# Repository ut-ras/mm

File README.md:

# Micromouse 2019
UT RAS Micromouse repository for 2019

The repository is structured with hardware eagle files under the [pcb](./pcb) directory and the esp-idf projects under the [software/test-programs](./software/test-programs) directory. To make or flash a program move into a project folder corresponding to that program and run either `make` or `make flash` respectively.
## Setup Software
- Download and Install esp-idf which can be found [here](https://docs.espressif.com/projects/esp-idf/en/latest/get-started/#setting-up-development-environment)
- Download and build software
```bash
git clone https://github.com/ut-ras/mm19
cd software
make
```

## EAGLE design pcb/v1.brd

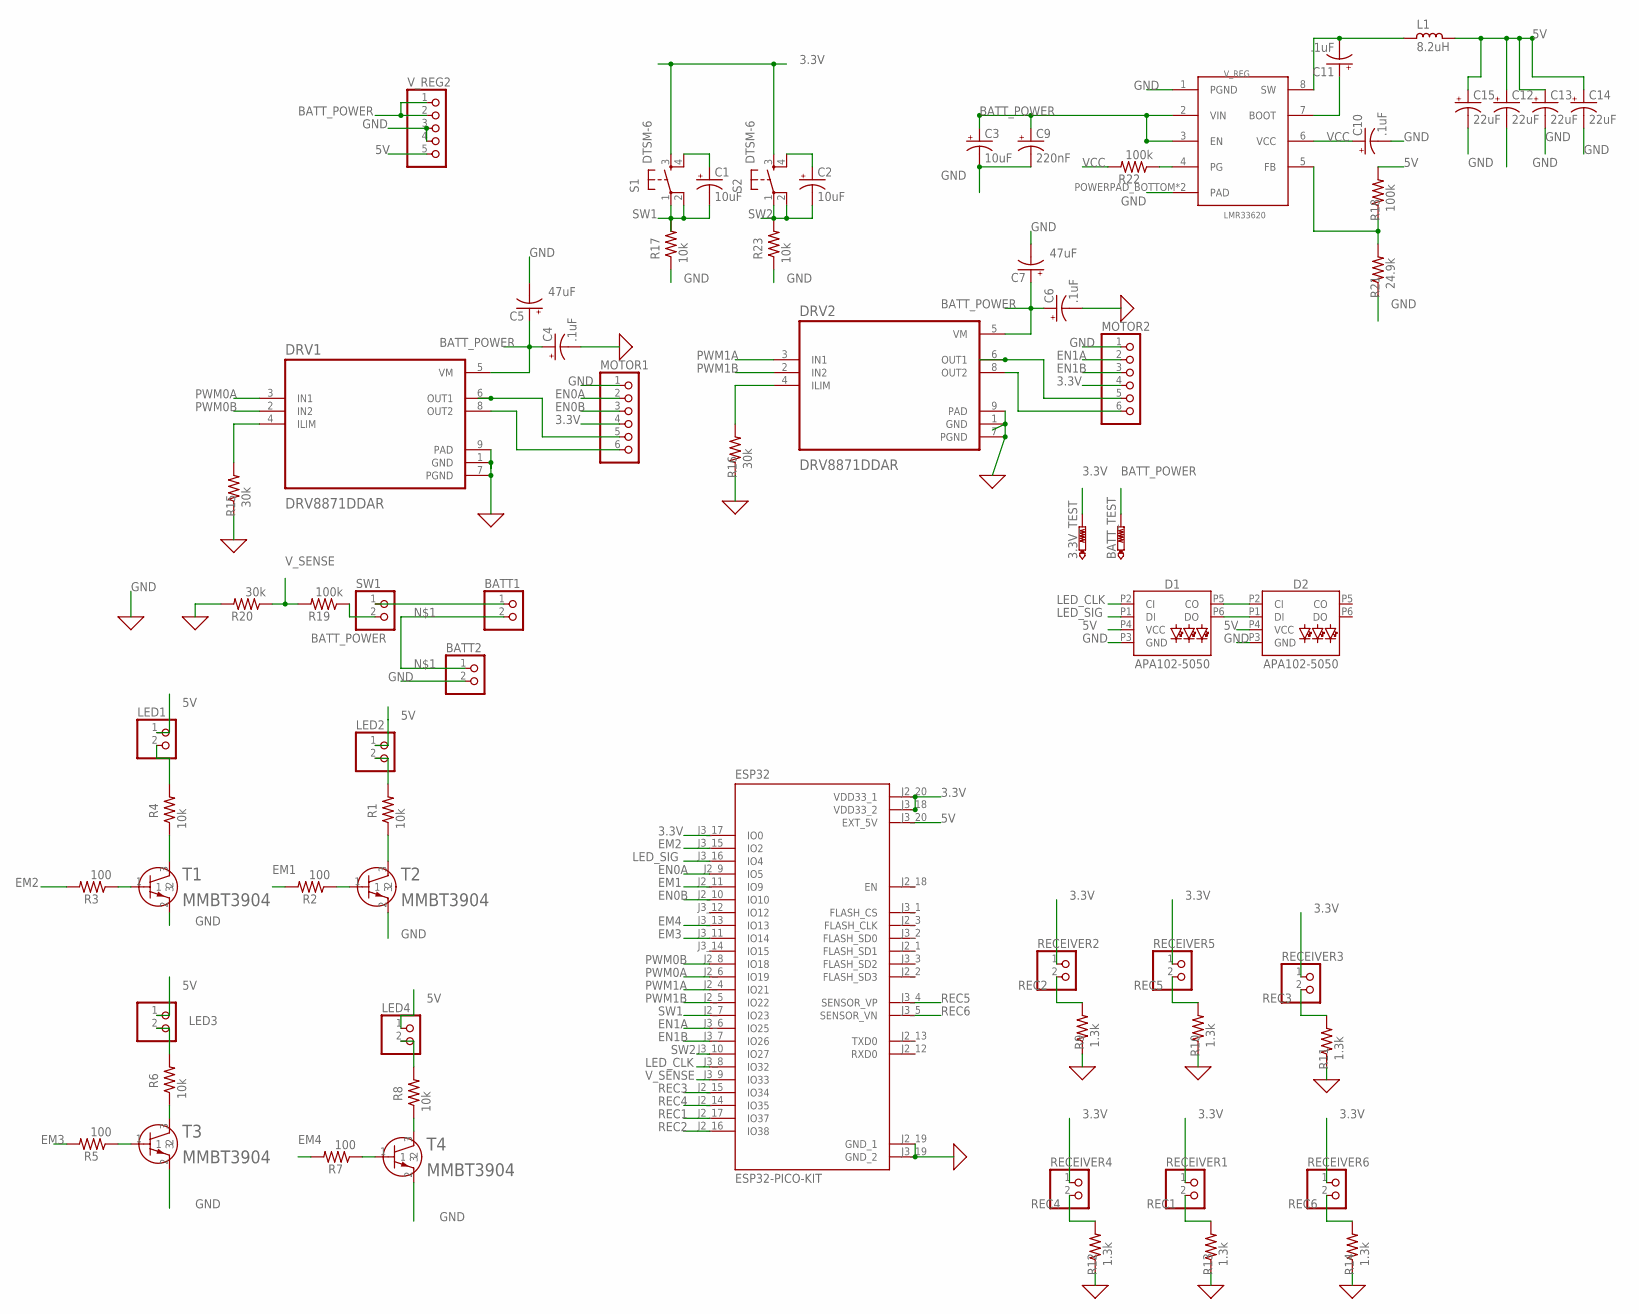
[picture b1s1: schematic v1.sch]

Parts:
3.3V_TEST: PTR1B1,27; B1,27
BATT1, BATT2: PINHD-1X2; 1X02
BATT_TEST: PTR1B1,27; B1,27
C1, C2, C3: 10uF; A/3216-18R
C4, C6, C10, C11: .1uF; A/3216-18R
C5, C7: 47uF; 150CLZ-0810
C9: 220nF; A/3216-18R
C12, C13, C14, C15: 22uF; A/3216-18R
D1, D2: APA102-5050
DRV1, DRV2: DRV8871DDAR; SOIC127P600X170-8N
ESP32: ESP32-PICO-KIT; XCVR_ESP32-PICO-KIT
L1: 8.2uH; PM1812
LED1, LED2, LED3, LED4: PINHD-1X2; 1X02
MOTOR1, MOTOR2: PINHD-1X6; 1X06
R1, R4, R6, R8, R17, R23: 10k; M1206
R2, R3, R5, R7: 100; M1206
R9, R10, R11, R12, R13, R14: 1.3k; M1206
R15, R16, R20: 30k; M1206
R18, R19, R22: 100k; M1206
R21: 24.9k; M1206
RECEIVER1, RECEIVER2, RECEIVER3, RECEIVER4, RECEIVER5, RECEIVER6: PINHD-1X2; 1X02
S1, S2: DTSM-6
SW1: PINHD-1X2; 1X02
T1, T2, T3, T4: MMBT3904; SOT23
V_REG: LMR33620; SO-8_POWERPAD
V_REG2: PINHD-1X5; 1X05

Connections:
3.3V: 3.3V_TEST.TP, ESP32.J2_20 (VDD33_1), ESP32.J3_17 (IO0), ESP32.J3_18 (VDD33_2), MOTOR1.4, MOTOR2.4, RECEIVER1.1, RECEIVER2.1, RECEIVER3.1, RECEIVER4.1, RECEIVER5.1, RECEIVER6.1, S1.3, S2.3
5V: C12.+, C13.+, C14.+, C15.+, D1.P4 (VCC), D2.P4 (VCC), ESP32.J3_20 (EXT_5V), L1.1, LED1.1, LED2.1, LED3.1, LED4.1, R18.2, V_REG2.5
BATT_POWER: BATT_TEST.TP, C3.+, C4.+, C5.+, C6.+, C7.+, C9.+, DRV1.5 (VM), DRV2.5 (VM), R19.1, SW1.2, V_REG.2 (VIN), V_REG.3 (EN), V_REG2.1, V_REG2.2
EM1: ESP32.J2_11 (IO9), R2.2
EM2: ESP32.J3_15 (IO2), R3.2
EM3: ESP32.J3_11 (IO14), R5.2
EM4: ESP32.J3_13 (IO13), R7.2
EN0A: ESP32.J2_9 (IO5), MOTOR1.2
EN0B: ESP32.J2_10 (IO10), MOTOR1.3
EN1A: ESP32.J3_6 (IO25), MOTOR2.2
EN1B: ESP32.J3_7 (IO26), MOTOR2.3
GND: BATT2.2, C3.-, C4.-, C5.-, C6.-, C7.-, C9.-, C10.-, C12.-, C13.-, C14.-, C15.-, D1.P3 (GND), D2.P3 (GND), DRV1.1 (GND), DRV1.7 (PGND), DRV1.9 (PAD), DRV2.1 (GND), DRV2.7 (PGND), DRV2.9 (PAD), ESP32.J2_19 (GND_1), ESP32.J3_19 (GND_2), MOTOR1.1, MOTOR2.1, R9.1, R10.1, R11.1, R12.1, R13.1, R14.1, R15.1, R16.1, R17.1, R20.2, R21.1, R23.1, T1.2, T2.2, T3.2, T4.2, V_REG.1 (PGND), V_REG.POWERPAD_BOTTOM (PAD), V_REG.POWERPAD_TOP (PAD), V_REG2.3, V_REG2.4
LED3: LED3.2, R6.2
LED_CLK: D1.P2 (CI), ESP32.J3_8 (IO32)
LED_SIG: D1.P1 (DI), ESP32.J3_16 (IO4)
unnamed: BATT1.2, BATT2.1
unnamed: BATT1.1, SW1.1
unnamed: C1.+, S1.4
unnamed: R2.1, T2.1
unnamed: LED2.2, R1.2
unnamed: R1.1, T2.3
unnamed: LED1.2, R4.2
unnamed: R4.1, T1.3
unnamed: R5.1, T3.1
unnamed: R6.1, T3.3
unnamed: R7.1, T4.1
unnamed: LED4.2, R8.2
unnamed: R8.1, T4.3
unnamed: DRV1.8 (OUT2), MOTOR1.6
unnamed: DRV1.6 (OUT1), MOTOR1.5
unnamed: DRV2.8 (OUT2), MOTOR2.6
unnamed: DRV2.6 (OUT1), MOTOR2.5
unnamed: DRV2.4 (ILIM), R16.2
unnamed: C2.+, S2.4
unnamed: R18.1, R21.2, V_REG.5 (FB)
unnamed: DRV1.4 (ILIM), R15.2
unnamed: C11.+, V_REG.7 (BOOT)
unnamed: C11.-, L1.2, V_REG.8 (SW)
unnamed: D1.P5 (CO), D2.P2 (CI)
unnamed: D1.P6 (DO), D2.P1 (DI)
PG: R22.1, V_REG.4 (PG)
PWM0A: DRV1.3 (IN1), ESP32.J2_6 (IO19)
PWM0B: DRV1.2 (IN2), ESP32.J2_8 (IO18)
PWM1A: DRV2.3 (IN1), ESP32.J2_4 (IO21)
PWM1B: DRV2.2 (IN2), ESP32.J2_5 (IO22)
REC1: ESP32.J2_17 (IO37), R13.2, RECEIVER1.2
REC2: ESP32.J2_16 (IO38), R9.2, RECEIVER2.2
REC3: ESP32.J2_15 (IO34), R11.2, RECEIVER3.2
REC4: ESP32.J2_14 (IO35), R12.2, RECEIVER4.2
REC5: ESP32.J3_4 (SENSOR_VP), R10.2, RECEIVER5.2
REC6: ESP32.J3_5 (SENSOR_VN), R14.2, RECEIVER6.2
SW1: C1.-, ESP32.J2_7 (IO23), R17.2, S1.1, S1.2
SW2: C2.-, ESP32.J3_10 (IO27), R23.2, S2.1, S2.2
T1: R3.1, T1.1
VCC: C10.+, R22.2, V_REG.6 (VCC)
V_SENSE: ESP32.J3_9 (IO33), R19.2, R20.1

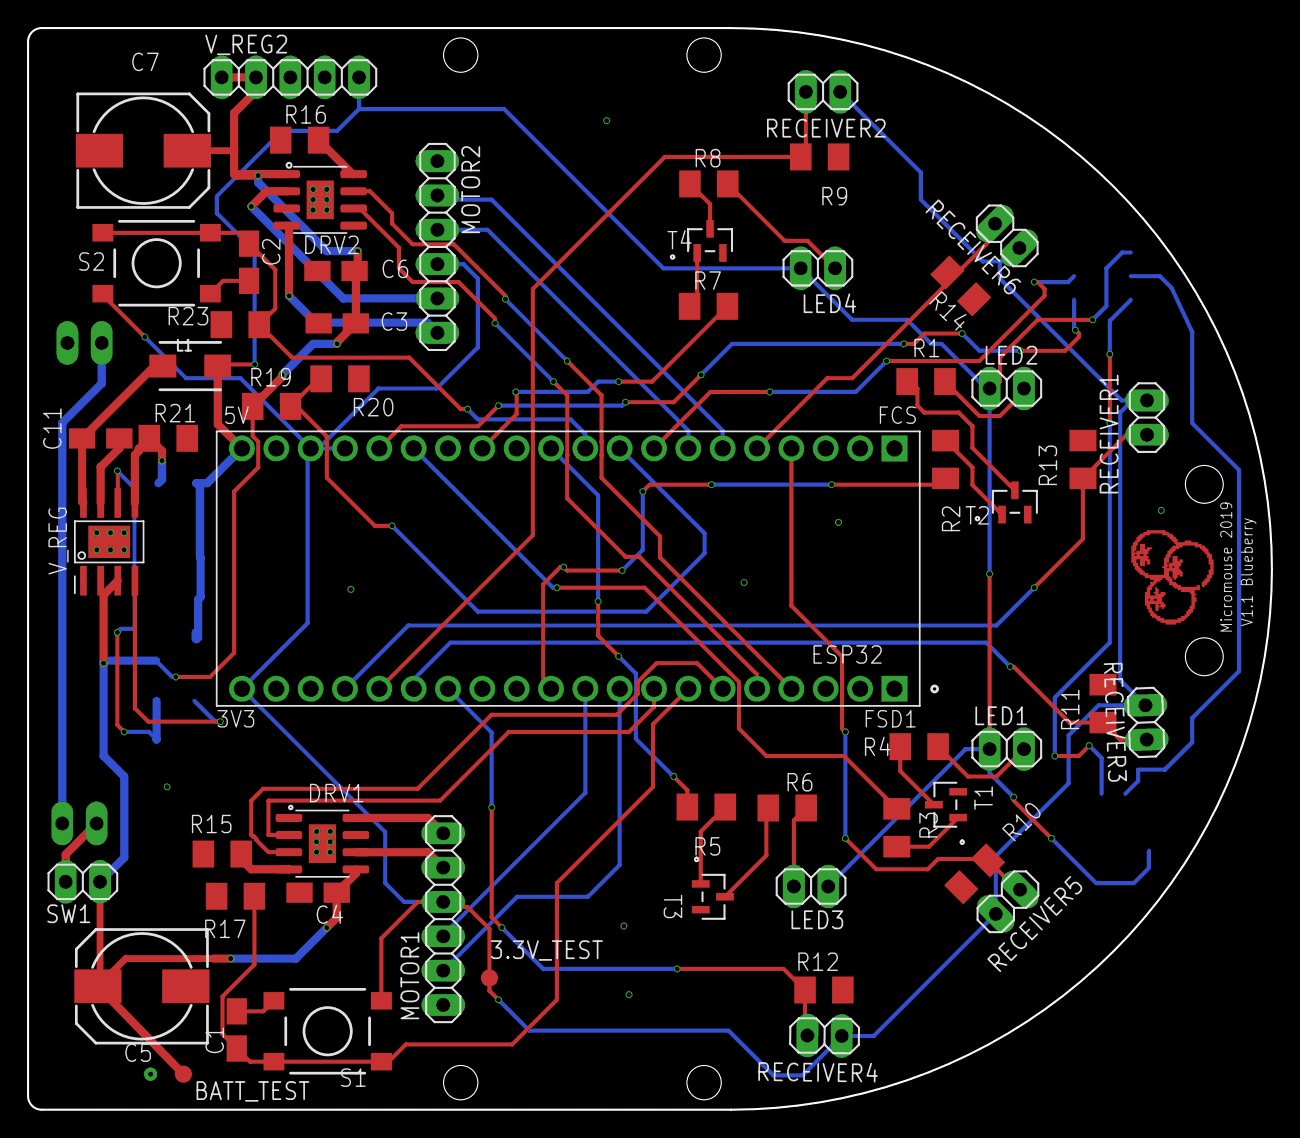
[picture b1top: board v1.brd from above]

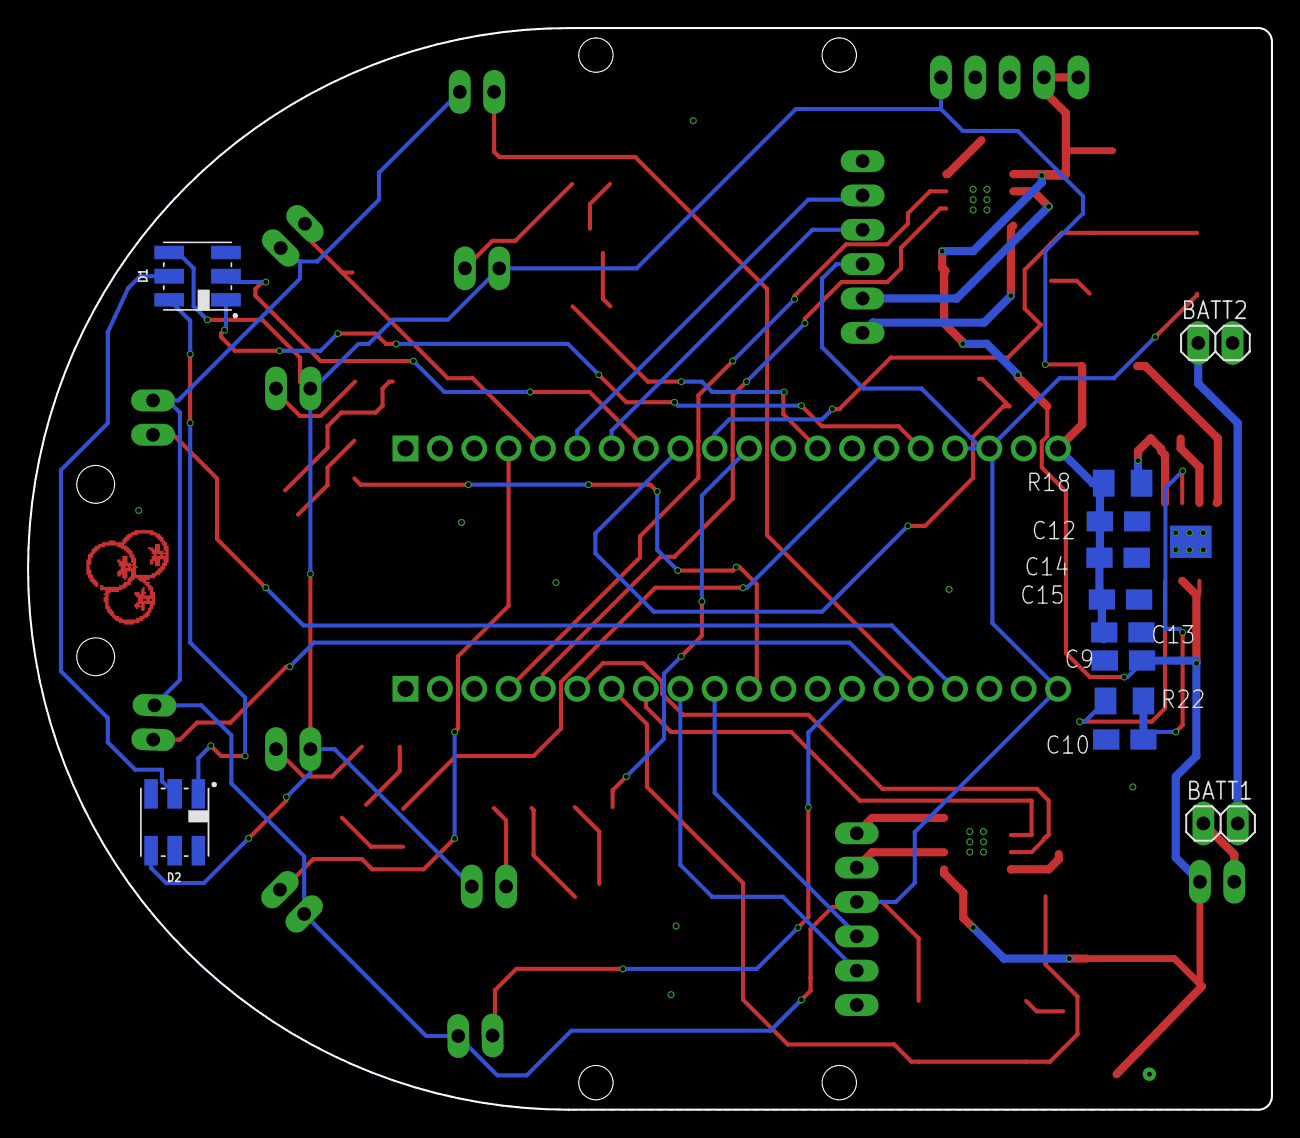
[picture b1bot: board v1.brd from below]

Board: 2 copper layers, 92.0 x 80.0 mm, 68 parts (12 on the bottom side), 56 nets.

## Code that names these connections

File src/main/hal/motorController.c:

#include "driver/mcpwm.h"

#define GPIO_PWM0A_OUT 19  // Set GPIO 19 as PWM0A
#define GPIO_PWM0B_OUT 18  // Set GPIO 18 as PWM0B
#define GPIO_PWM1A_OUT 22  // Set GPIO 22 as PWM1A
#define GPIO_PWM1B_OUT 21  // Set GPIO 21 as PWM1B

/**
 * @brief Configure whole MCPWM module
 */
static void mcpwm_frequency_initialize() {
  mcpwm_config_t pwm_config;
  pwm_config.frequency = 100;  // frequency = 100Hz
  pwm_config.cmpr_a = 0.0;     // duty cycle of PWMxA = 0.0%
  pwm_config.cmpr_b = 0.0;     // duty cycle of PWMxb = 0.0%
  pwm_config.counter_mode = MCPWM_UP_COUNTER;
  pwm_config.duty_mode = MCPWM_DUTY_MODE_0;
  mcpwm_init(
      MCPWM_UNIT_0, MCPWM_TIMER_0,
      &pwm_config);  // Configure PWM0A(19) & PWM0B(18) with above settings
  // connect 19 and 18 to a single motors
  pwm_config.frequency = 100;  // frequency = 100Hz
  pwm_config.cmpr_a = 0.0;     // duty cycle of PWMxA = 0.0%
  pwm_config.cmpr_b = 0.0;     // duty cycle of PWMxb = 0.0%
  pwm_config.counter_mode = MCPWM_UP_COUNTER;
  pwm_config.duty_mode = MCPWM_DUTY_MODE_0;
  mcpwm_init(
      MCPWM_UNIT_0, MCPWM_TIMER_1,
      &pwm_config);  // Configure PWM1A(21) & PWM1B(22) with above settings
}

/*
 * Call this initialize before starting to set speed of the both motors
 */
void mcpwm_initialize() {
  printf("initializing mcpwm gpio...\n");
  mcpwm_gpio_init(MCPWM_UNIT_0, MCPWM0A, GPIO_PWM0A_OUT);
  mcpwm_gpio_init(MCPWM_UNIT_0, MCPWM0B, GPIO_PWM0B_OUT);
  mcpwm_gpio_init(MCPWM_UNIT_0, MCPWM1A, GPIO_PWM1A_OUT);
  mcpwm_gpio_init(MCPWM_UNIT_0, MCPWM1B, GPIO_PWM1B_OUT);
  mcpwm_frequency_initialize();
}

// speed is positive to go forward, negative to go backward. -100 to 100.
void setLeftSpeed(double speed) {
  if (speed > 0) {
    mcpwm_set_signal_low(MCPWM_UNIT_0, MCPWM_TIMER_1, MCPWM_OPR_B);
    mcpwm_set_duty(MCPWM_UNIT_0, MCPWM_TIMER_1, MCPWM_OPR_A, speed);
    mcpwm_set_duty_type(MCPWM_UNIT_0, MCPWM_TIMER_1, MCPWM_OPR_A,
                        MCPWM_DUTY_MODE_0);
  } else {
    mcpwm_set_signal_low(MCPWM_UNIT_0, MCPWM_TIMER_1, MCPWM_OPR_A);
    mcpwm_set_duty(MCPWM_UNIT_0, MCPWM_TIMER_1, MCPWM_OPR_B, -speed);
    mcpwm_set_duty_type(MCPWM_UNIT_0, MCPWM_TIMER_1, MCPWM_OPR_B,
                        MCPWM_DUTY_MODE_0);
  }
}

// speed is positive to go forward, negative to go backward. -100 to 100.
void setRightSpeed(double speed) {
  if (speed > 0) {
    mcpwm_set_signal_low(MCPWM_UNIT_0, MCPWM_TIMER_0, MCPWM_OPR_B);
    mcpwm_set_duty(MCPWM_UNIT_0, MCPWM_TIMER_0, MCPWM_OPR_A, speed);
    mcpwm_set_duty_type(MCPWM_UNIT_0, MCPWM_TIMER_0, MCPWM_OPR_A,
                        MCPWM_DUTY_MODE_0);
  } else {
    mcpwm_set_signal_low(MCPWM_UNIT_0, MCPWM_TIMER_0, MCPWM_OPR_A);
    mcpwm_set_duty(MCPWM_UNIT_0, MCPWM_TIMER_0, MCPWM_OPR_B, -speed);
    mcpwm_set_duty_type(MCPWM_UNIT_0, MCPWM_TIMER_0, MCPWM_OPR_B,
                        MCPWM_DUTY_MODE_0);
  }
}

void setMotors(float left, float right) {
  setLeftSpeed(left);
  setRightSpeed(-right);
}

void stopMotors(void) { setMotors(0.0, 0.0); }

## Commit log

2018-10-19 added high level algorithm and function implementations for simulator testing
2018-10-24 first commit. V1.0 implementation of classes for the simulation and C/C++ conversion. Documented. Needs driver with algorithm rebuilt. Needs basic testing driver.
2018-10-26 main algorithm v2 complete (probably), needs testing in simulator
2018-10-31 Added ADC testing files for esp
2018-11-08 updated working class and algorithm files for mm, now to translate into C and continue testing
2018-11-30 commited start of C port
2018-11-30 Neighbor.h, .c compiles
2018-11-30 unit tested, works
2018-12-01 updating Mouse.c...
2018-12-01 removed bool for Neighbor, replaced with a -1, 0, 1 and a #define UNKNOWN, TRUE, FALSE in the main mouse method that uses neighbor's pathbool; cleaned up control flow for findDir in mouse.c
2018-12-01 finished implementing what I can for Mouse.h, needs low level movement functions and abstracted testing moving functions as well as unit testing. Also needs Node.c to be implemented.
2018-12-08 wrote up node.c, alterations to neighbor, built a main tester and a makefile, currently unit testing looks good, needs to finish implmenting and rebuilding addRelation method of node.c, also testing 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
2018-12-08 rebuilt main to test cohesive classes, edited makefile, works, needs sensor functions to test actual mazesolving, also addrelations needs to be completed
2018-12-31 Added ESP initial files
2019-01-03 setup basic working client for c port of mmsim, processes wall commands and movement
2019-01-26 removed testing code that used weird ESP stuff
2019-02-20 commit from local before disk wipe
2019-02-20 untested hal code
2019-03-09 starting structure implementation of cpp port
2019-03-30 working encoders
2019-03-30 initialize second encoder
2019-03-30 detect stop as a direction
2019-03-30 Fixed merge conflig
2019-04-03 Cleaned up and organized hal #2
2019-04-04 additional refactoring
2019-04-08 Changed 5V receiver inputs to 3.3V
2019-04-08 Added Smd led
2019-04-08 Fixed led positioning and adc pins
2019-04-08 Changed 5V line
2019-04-08 Changed pin placement
2019-04-08 Flipped the back sensor resistors
2019-04-08 Evened out the holes to make pcb look nicer
2019-04-10 Changed the voltage regulator and updated the pcb
2019-04-10 Changed the resistive voltage divider values
2019-04-10 Added ground plane
2019-04-13 Added Strawberry
2019-04-13 initial pid code, pid_ctl unfinished
2019-04-13 Changed strawberry and caps. Added gerber files
2019-04-13 Last minute touches to PCB Moved headers for motor and led to not interfere with nuts. Made ground plane solid instead of hatched. Fixed silkscreen overlap. Connected ground planes for top and bottom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
2019-04-19 implementing mouse, maze, cut down maze functions for a cheaper query function
2019-04-20 initial pid_ctl
2019-04-21 removed deprecated folders and code.
2019-04-27 starting sim debugging
2019-04-30 Cpp sim working: compiles->links->basic maze testing complete. Starting file style standardization and basic mouse functionality testing.
2019-04-30 built basic movement test, added mouse to displayMaze, preparing for Mouse.cpp integration with HAL.
2019-05-10 in progress of comprehensive algorithm test. retroactively added mmsim bin and run.sh script to automate compiling and cleaning.
2019-05-10 fixed possible mod error with negative numbers.
2019-05-10 removed algo files again, fixed compiler issues
2019-05-10 add documentation for pid and enc code
2019-05-14 Updated movement
2019-05-14 Finished structure for moveIR
2019-05-14 Changed PCB
    Fixes #11
    Fixes #10
    Fixes #9
    Fixes #8
2019-05-14 Cosmetic Changes
2019-05-14 Fixed direction of motor
2019-05-14 blueberry: not 🍅
2019-05-14 blueberry: 📐
2019-05-21 Made connnecting grounds
2019-05-21 Changed ground plane
2019-05-21 Removed overlap
2019-05-21 Changed locations of the holes
2019-05-24 added more profile info for sim (wall input data, moved maze output after algorithm decision), fixed Maze::query() x|y swap, remapped Algorithm::getCheck() input call. Fixed bug where wall informatio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
2019-05-24 added infinite loop unless appropriate key is pressed for run simulation. New Bug: Algorithm seems to run in loops. Also, unix/linux specific system call for clear screen. Needs to have a check for w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
2019-05-24 Added sensortest and started testing correction for moveIR
2019-05-24 unknown commit
2019-05-24 unfixed part of unknown commit, added debugging status on algorithm side, bug narrowed down to output decision not corresponding with internal decision.
2019-05-24 added int var for algorithm use in simulator.
2019-05-25 added mouse position parameters to getCheck call in simulator.
2019-05-25 added debugging back in: DO NOT DELETE AHMAD, fixed bad input parameter type int to bool for walls
2019-05-27 Started turning move and turn
2019-05-28 Tuned PID values and fixed bug related to IR Zeros
2019-05-28 fixed parameter types for algorithm again.
2019-05-29 Updated values and added delay after each movement
2019-05-30 misc: clang-format + .gitignore things
    and a precommit hook!
    If you reached this commit while trying to trace through the commit history, I'm sorry.
2019-05-30 build-sys: some mild restructuring
    This system is mostly identical to the one in [glowing-potato](https://github.com/rrbutani/glowing-potato).
    We get our own components dir and a folder with projects in it.
2019-05-30 hal: add an example stub and the necessary build-system things
2019-05-30 hal: add a pin-map component stub
2019-05-30 build-sys: add support for contributed components
2019-05-30 build-sys: add a handy top level Makefile
    This lets us build a target across all the esp-idf projects in the repo which is nice for compdb things (it's also convenient).
2019-05-30 misc: cleanup
2019-05-31 "Basic move encoder code"
2019-05-31 Added enctest and changed constants
2019-05-31 build-sys: added a format target to the top level Makefile
    I left the attempts in for the curious; I'll remove them in the next commit.
2019-05-31 build-sys: misc
2019-05-31 build-sys: update the precommit hook to be friendlier
2019-06-01 Cleaned PID to work with wall follow
    TODO tune the turning because MAX_SUM was change
2019-06-01 Added nav, fixed moveEnc and changed PID values
2019-06-02 Added turn any degrees
2019-06-02 lights: first pass
2019-06-02 MMoved all IR reads to getWalls
2019-06-02 EExposed moveCeneter
2019-06-02 EAdded turn functions to nav
2019-06-02 Added timeout
2019-06-02 mc: add a braking option
2019-06-02 pid: changes to turn90
2019-06-02 misc: assorted changes
2019-06-02 added working algorithm to mouse, edited mouse interface to remove double heading, built basic mouse_test. ready for compiling and testing.
2019-06-02 pid: untested changes :-)
2019-06-02 Code compiles
2019-06-02 Cleaned up organization
2019-06-02 lights: now in the library
2019-06-02 mtesting turn180
2019-06-02 Added unit movement
2019-06-02 Minor constant changes
2019-06-02 added updated algorithm
2019-06-02 Basic Functionality
2019-06-02 Added hhardcoded movement
2019-06-02 AChanged nav to only move one square
2019-06-02 Merged compoenents
2019-06-02 CChanged one unit
2019-06-02 Changed constants
2019-06-02 changed
2019-06-02 added initial wall conditions for first data input to algo
2019-06-02 updated speed
2019-06-02 call to movement getWalls in getCheck for mouse.
2019-06-02 flip wall logic from movement.
2019-06-02 added internal move to mouse rotate
2019-06-02 removed potential sources of out[0] = 3 error.
2019-06-08 Constant changes
2019-06-09 Add stuff to readme
    I'm sure @rrbutani can put in more detail regarding build things you can do.
2019-06-09 removed extraneous comments, hamming dist data structure.

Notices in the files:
parts and their libraries:
SparkFun-LED: Licensing: Creative Commons ShareAlike 4.0 International - https://creativecommons.org/licenses/by-sa/4.0
rc-master-smd: Copyright (C) 2007, Bob Starr
